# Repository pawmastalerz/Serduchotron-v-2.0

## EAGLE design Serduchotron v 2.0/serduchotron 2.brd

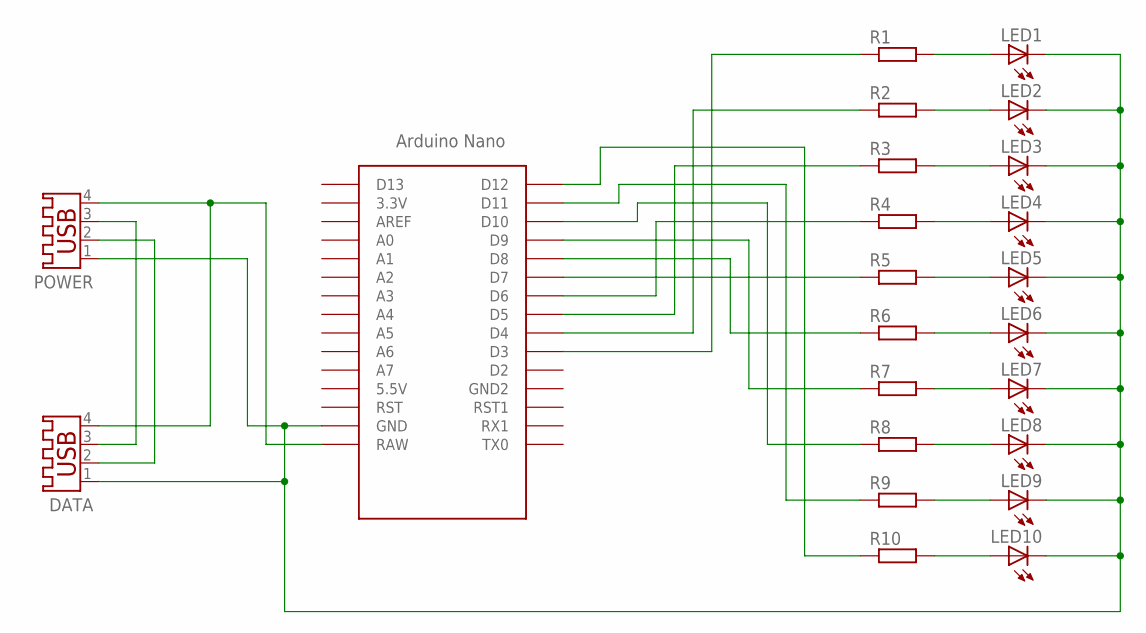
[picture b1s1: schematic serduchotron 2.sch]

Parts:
DATA: USB-A003
LED1, LED2, LED3, LED4, LED5, LED6, LED7, LED8, LED9, LED10: LEDCHIP-LED0805; CHIP-LED0805
POWER: USB-A003
R1, R2, R3, R4, R5, R6, R7, R8, R9, R10: R-EU_M0805; M0805
U$1: NANO

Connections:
DATA+: DATA.2, POWER.2
DATA-: DATA.3, POWER.3
GND: DATA.1, LED1.C, LED2.C, LED3.C, LED4.C, LED5.C, LED6.C, LED7.C, LED8.C, LED9.C, LED10.C, POWER.1, U$1.GND
LED1: LED1.A, R1.2
LED2: LED2.A, R2.2
LED3: LED3.A, R3.2
LED4: LED4.A, R4.2
LED5: LED5.A, R5.2
LED6: LED6.A, R6.2
LED7: LED7.A, R7.2
LED8: LED8.A, R8.2
LED9: LED9.A, R9.2
LED10: LED10.A, R10.2
R1: R1.1, U$1.D3
R2: R2.1, U$1.D4
R3: R3.1, U$1.D5
R4: R4.1, U$1.D6
R5: R5.1, U$1.D7
R6: R6.1, U$1.D8
R7: R7.1, U$1.D9
R8: R8.1, U$1.D10
R9: R9.1, U$1.D11
R10: R10.1, U$1.D12
VCC: DATA.4, POWER.4, U$1.RAW

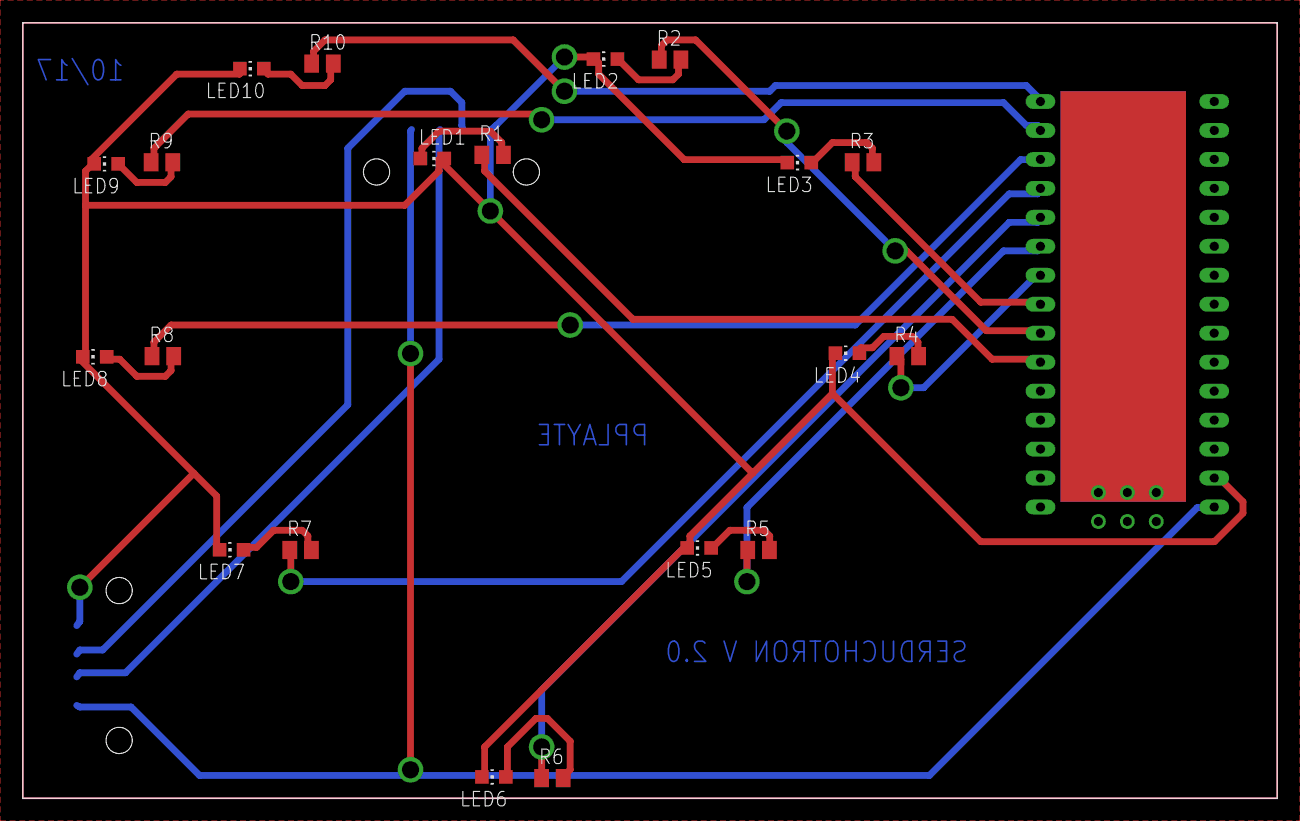
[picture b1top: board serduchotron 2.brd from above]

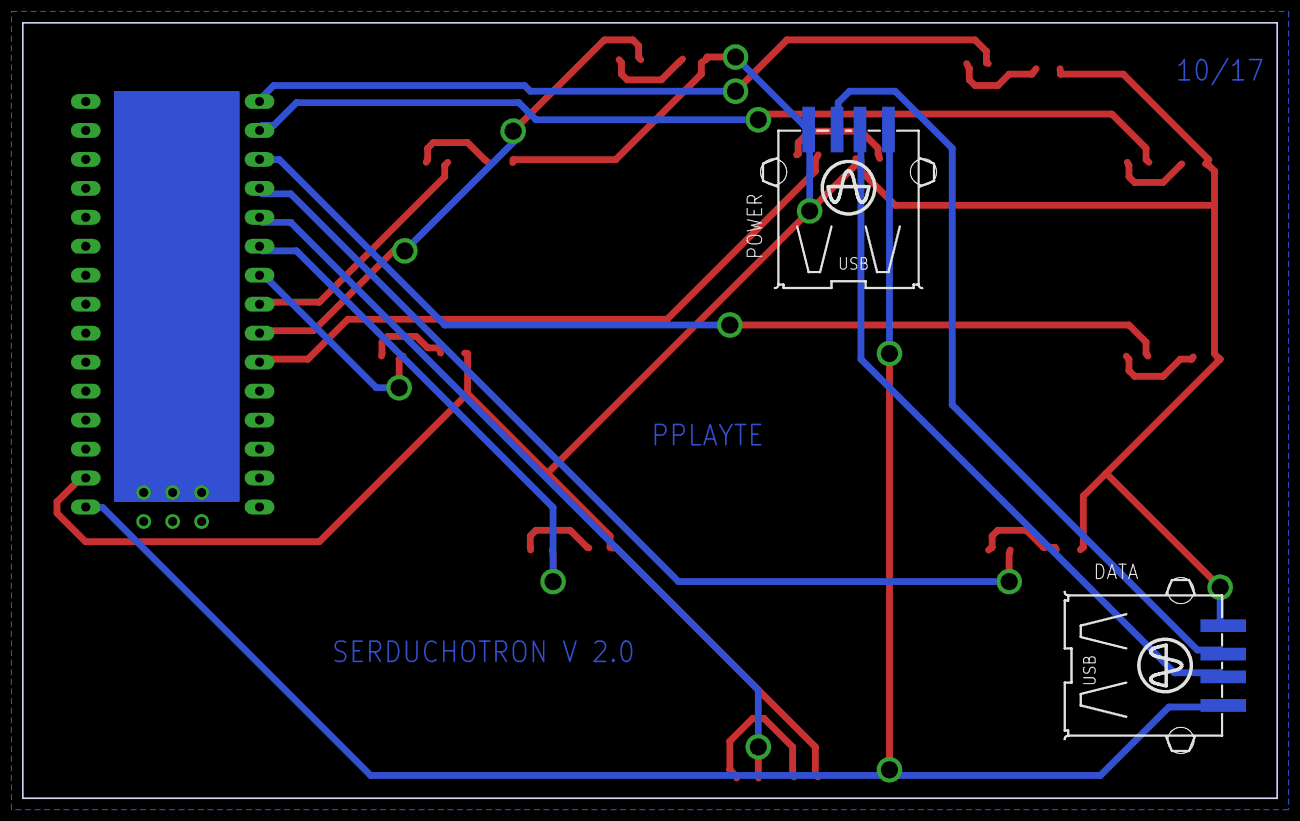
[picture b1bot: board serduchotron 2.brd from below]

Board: 2 copper layers, 110.0 x 68.0 mm, 23 parts (3 on the bottom side), 24 nets.

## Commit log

2017-10-05 Completed project.
